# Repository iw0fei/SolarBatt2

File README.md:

# SolarBatt2
Battery Monitor with ESP32 for photovoltaic system

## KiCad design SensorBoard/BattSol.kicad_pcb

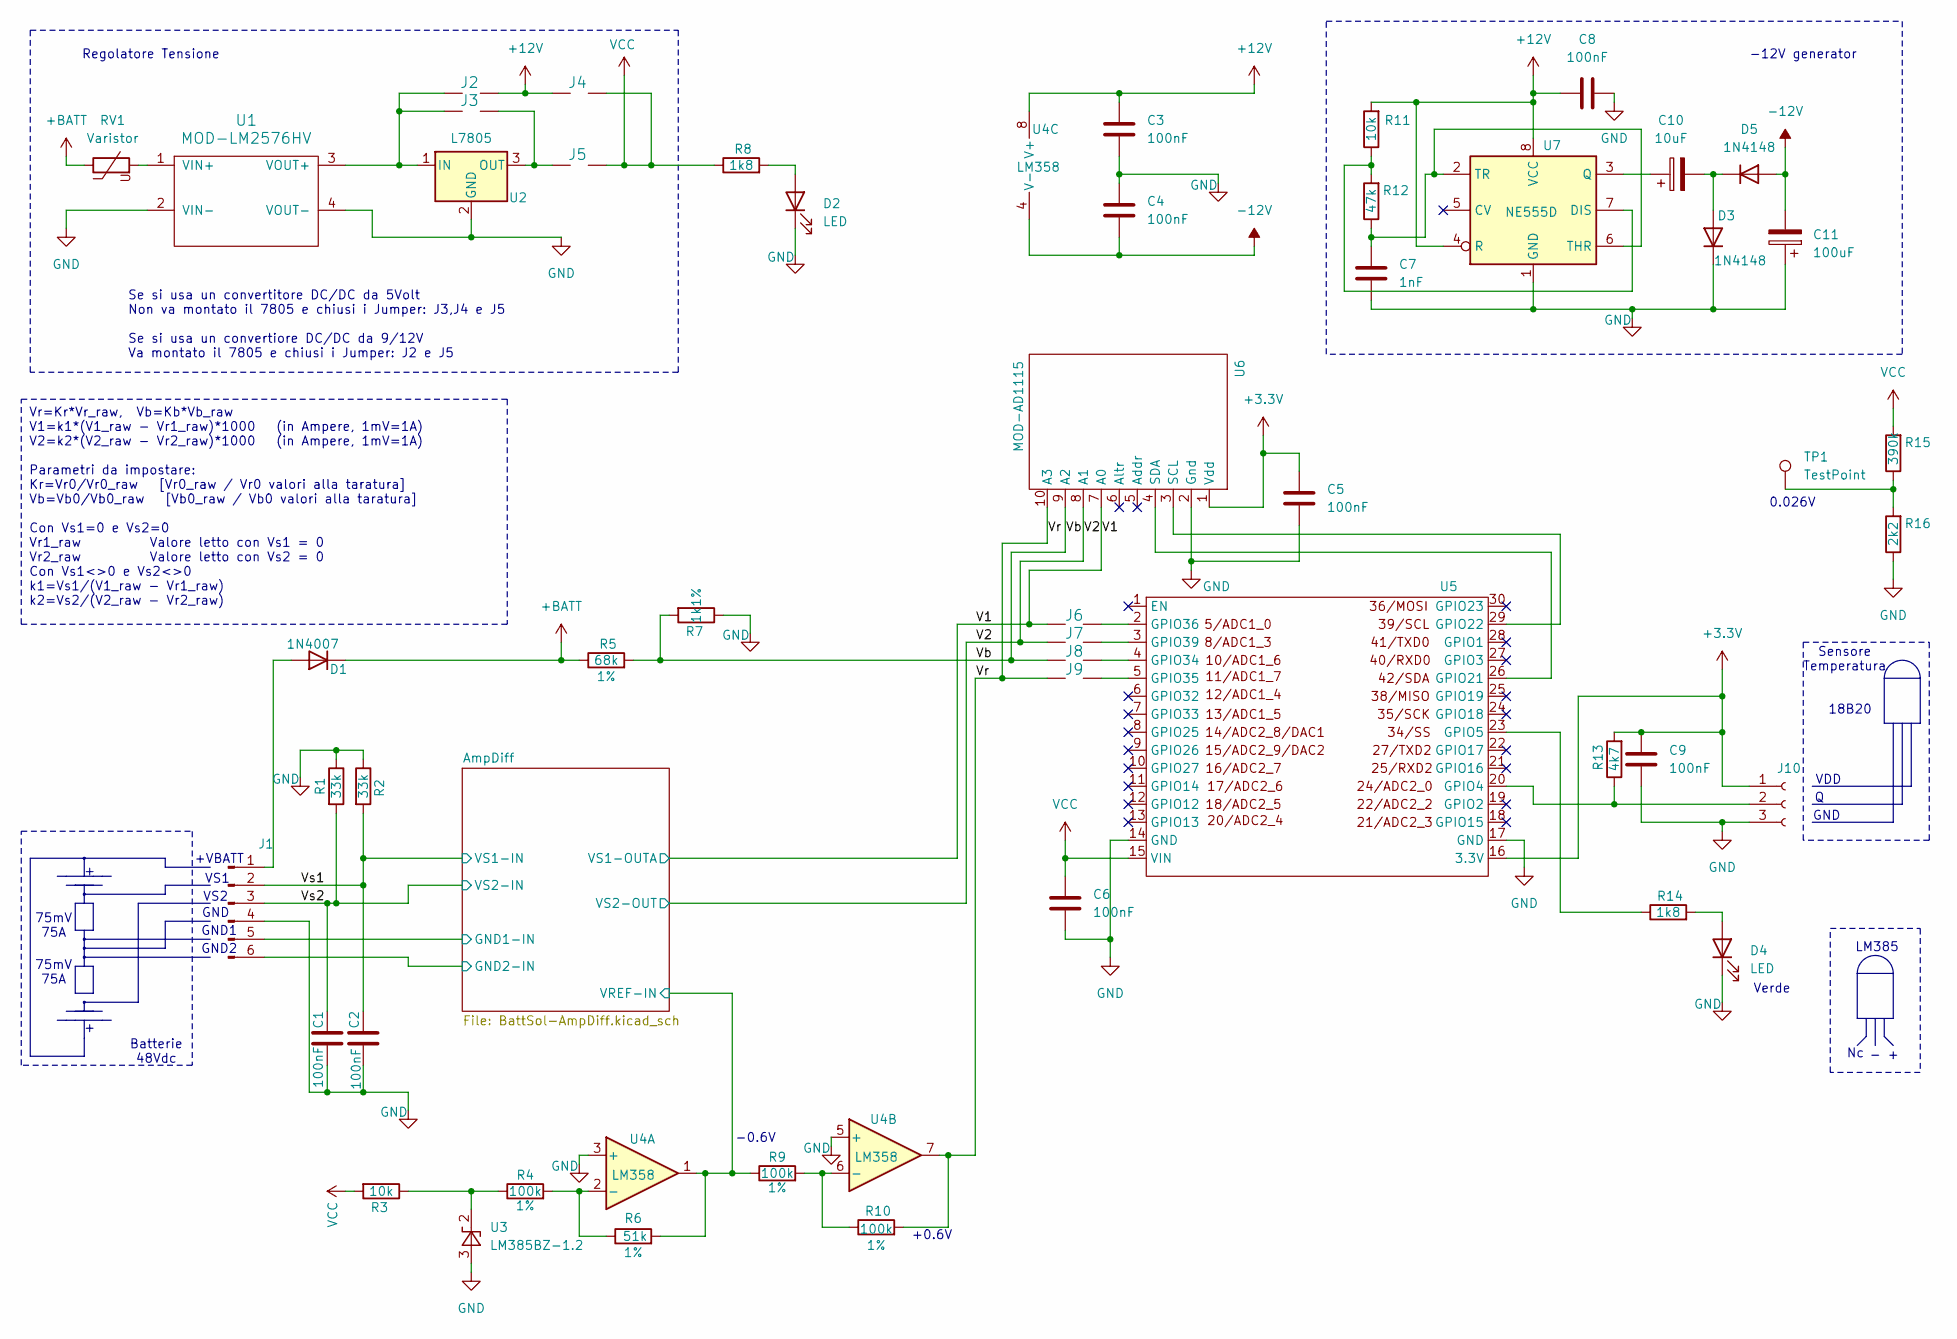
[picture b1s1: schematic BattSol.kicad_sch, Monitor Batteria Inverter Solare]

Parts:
C1, C2, C3, C4, C5, C6, C8, C9: 100nF; C_Rect_L4.6mm_W2.0mm_P2.50mm_MKS02_FKP02
C7: 1nF; C_Rect_L4.6mm_W2.0mm_P2.50mm_MKS02_FKP02
C10: 10uF; CP_Radial_D8.0mm_P5.00mm
C11: 100uF; CP_Radial_D8.0mm_P5.00mm
D1: 1N4007; D_DO-34_SOD68_P5.08mm_Vertical_AnodeUp
D2, D4: LED; LED_D4.0mm
D3, D5: 1N4148; D_DO-34_SOD68_P5.08mm_Vertical_AnodeUp
J1: Conn_01x06_Pin; XCONN_6
J2, J3, J4, J5, J6, J7, J8, J9: JUMPER; XCONN_2
J10: Conn_01x03_Socket; XCONN_3
R1, R2: 33k; R_Axial_DIN0207_L6.3mm_D2.5mm_P7.62mm_Horizontal
R3, R11: 10k; R_Axial_DIN0207_L6.3mm_D2.5mm_P7.62mm_Horizontal
R4, R9, R10: 100k; R_Axial_DIN0207_L6.3mm_D2.5mm_P7.62mm_Horizontal
R5: 68k; R_Axial_DIN0207_L6.3mm_D2.5mm_P7.62mm_Horizontal
R6: 51k; R_Axial_DIN0207_L6.3mm_D2.5mm_P7.62mm_Horizontal
R7: 1k; R_Axial_DIN0207_L6.3mm_D2.5mm_P7.62mm_Horizontal
R8, R14: 1k8; R_Axial_DIN0207_L6.3mm_D2.5mm_P7.62mm_Horizontal
R12: 47k; R_Axial_DIN0207_L6.3mm_D2.5mm_P7.62mm_Horizontal
R13: 4k7; R_Axial_DIN0207_L6.3mm_D2.5mm_P7.62mm_Horizontal
R15: 390k; R_Axial_DIN0207_L6.3mm_D2.5mm_P7.62mm_Horizontal
R16: 2k2; R_Axial_DIN0207_L6.3mm_D2.5mm_P7.62mm_Horizontal
RV1: Varistor; RV_Disc_D7mm_W3.4mm_P5mm
TP1: TestPoint; XCONN_1
U1: MOD-LM2576HV
U2: L7805; TO-3PB-3_Vertical
U3: LM385BZ-1.2; TO-92_Inline
U4: LM358; XDIL_8
U5: ESP32-DEVKIT-V1
U6: MOD-AD1115; MOD-ADS1115
U7: NE555D; CERDIP-8_W7.62mm_SideBrazed_LongPads

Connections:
+3.3V: C5.1, C9.1, J10.1, R13.2, U5.16 (3.3V), U6.1 (Vdd)
+12V: C3.1, C8.1, J2.2, J4.1, R11.2, U4.8 (V+), U7.4 (R), U7.8 (VCC); also elsewhere on the board
+BATT: D1.1 (K), R5.1, RV1.1
-12V: C4.2, C11.2, D5.2 (A), U4.4 (V-); also elsewhere on the board
/AmpDiff/GND1-IN: J1.5; also elsewhere on the board
/AmpDiff/GND2-IN: J1.6; also elsewhere on the board
/AmpDiff/VREF-IN: R6.2, R9.1, U4.1; also elsewhere on the board
/V1: J6.1, U6.7 (A0); also elsewhere on the board
/V2: J7.1, U6.8 (A1); also elsewhere on the board
/Vb: J8.1, R5.2, R7.2, U6.9 (A2)
/Vr: J9.1, R10.2, U4.7, U6.10 (A3)
/Vs1: C2.1, J1.2, R2.2; also elsewhere on the board
/Vs2: C1.1, J1.3, R1.2; also elsewhere on the board
GND: C1.2, C2.2, C3.2, C4.1, C5.2, C6.2, C7.2, C8.2, C9.2, C11.1, D2.1 (K), D3.1 (K), D4.1 (K), J1.4, J10.3, R1.1, R2.1, R7.1, R16.1, U1.2 (VIN-), U1.4 (VOUT-), U2.2 (GND), U3.3 (A), U4.3 (+), U4.5 (+), U5.14 (GND), U5.17 (GND), U6.2 (Gnd), U7.1 (GND); also elsewhere on the board
unnamed: D1.2 (A), J1.1
unnamed: D2.2 (A), R8.2
unnamed: C10.2, D3.2 (A), D5.1 (K)
unnamed: D4.2 (A), R14.2
unnamed: J10.2, R13.1, U5.20 (GPIO4)
unnamed: R15.1, R16.2, TP1.1
unnamed: RV1.2, U1.1 (VIN+)
unnamed: J2.1, J3.1, U1.3 (VOUT+), U2.1 (IN)
unnamed: J3.2, J5.1, U2.3 (OUT)
unnamed: R3.1, R4.1, U3.2 (K)
unnamed: R4.2, R6.1, U4.2 (-)
unnamed: R9.2, R10.1, U4.6 (-)
unnamed: R14.1, U5.23 (GPIO5)
unnamed: U5.26 (GPIO21), U6.4 (SDA)
unnamed: U5.29 (GPIO22), U6.3 (SCL)
unnamed: J8.2, U5.4 (GPIO34)
unnamed: J9.2, U5.5 (GPIO35)
unnamed: J6.2, U5.2 (GPIO36)
unnamed: J7.2, U5.3 (GPIO39)
unnamed: R11.1, R12.2, U7.7 (DIS)
unnamed: C10.1, U7.3 (Q)
unnamed: C7.1, R12.1, U7.2 (TR), U7.6 (THR)
VCC: C6.1, J4.2, J5.2, R3.2, R8.1, R15.2, U5.15 (VIN)

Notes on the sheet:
Vr=Kr*Vr_raw, Vb=Kb*Vb_raw V1=k1*(V1_raw - Vr1_raw)*1000 (in Ampere, 1mV=1A) V2=k2*(V2_raw - Vr2_raw)*1000 (in Ampere, 1mV=1A) Parametri da impostare: Kr=Vr0/Vr0_raw [Vr0_raw / Vr0 valori alla taratura] Vb=Vb0/Vb0_raw [Vb0_raw / Vb0 valori alla taratura] Con Vs1=0 e Vs2=0 Vr1_raw Valore letto con V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
VS2
0.026V
Verde
-12V generator
+0.6V
VS1
75mV 75A
Se si usa un convertitore DC/DC da 5Volt Non va montato il 7805 e chiusi i Jumper: J3,J4 e J5 Se si usa un convertiore DC/DC da 9/12V Va montato il 7805 e chiusi i Jumper: J2 e J5
GND1
Regolatore Tensione
18B20
+VBATT
VDD
Sensore Temperatura
GND
LM385
Batterie 48Vdc
GND2
-0.6V

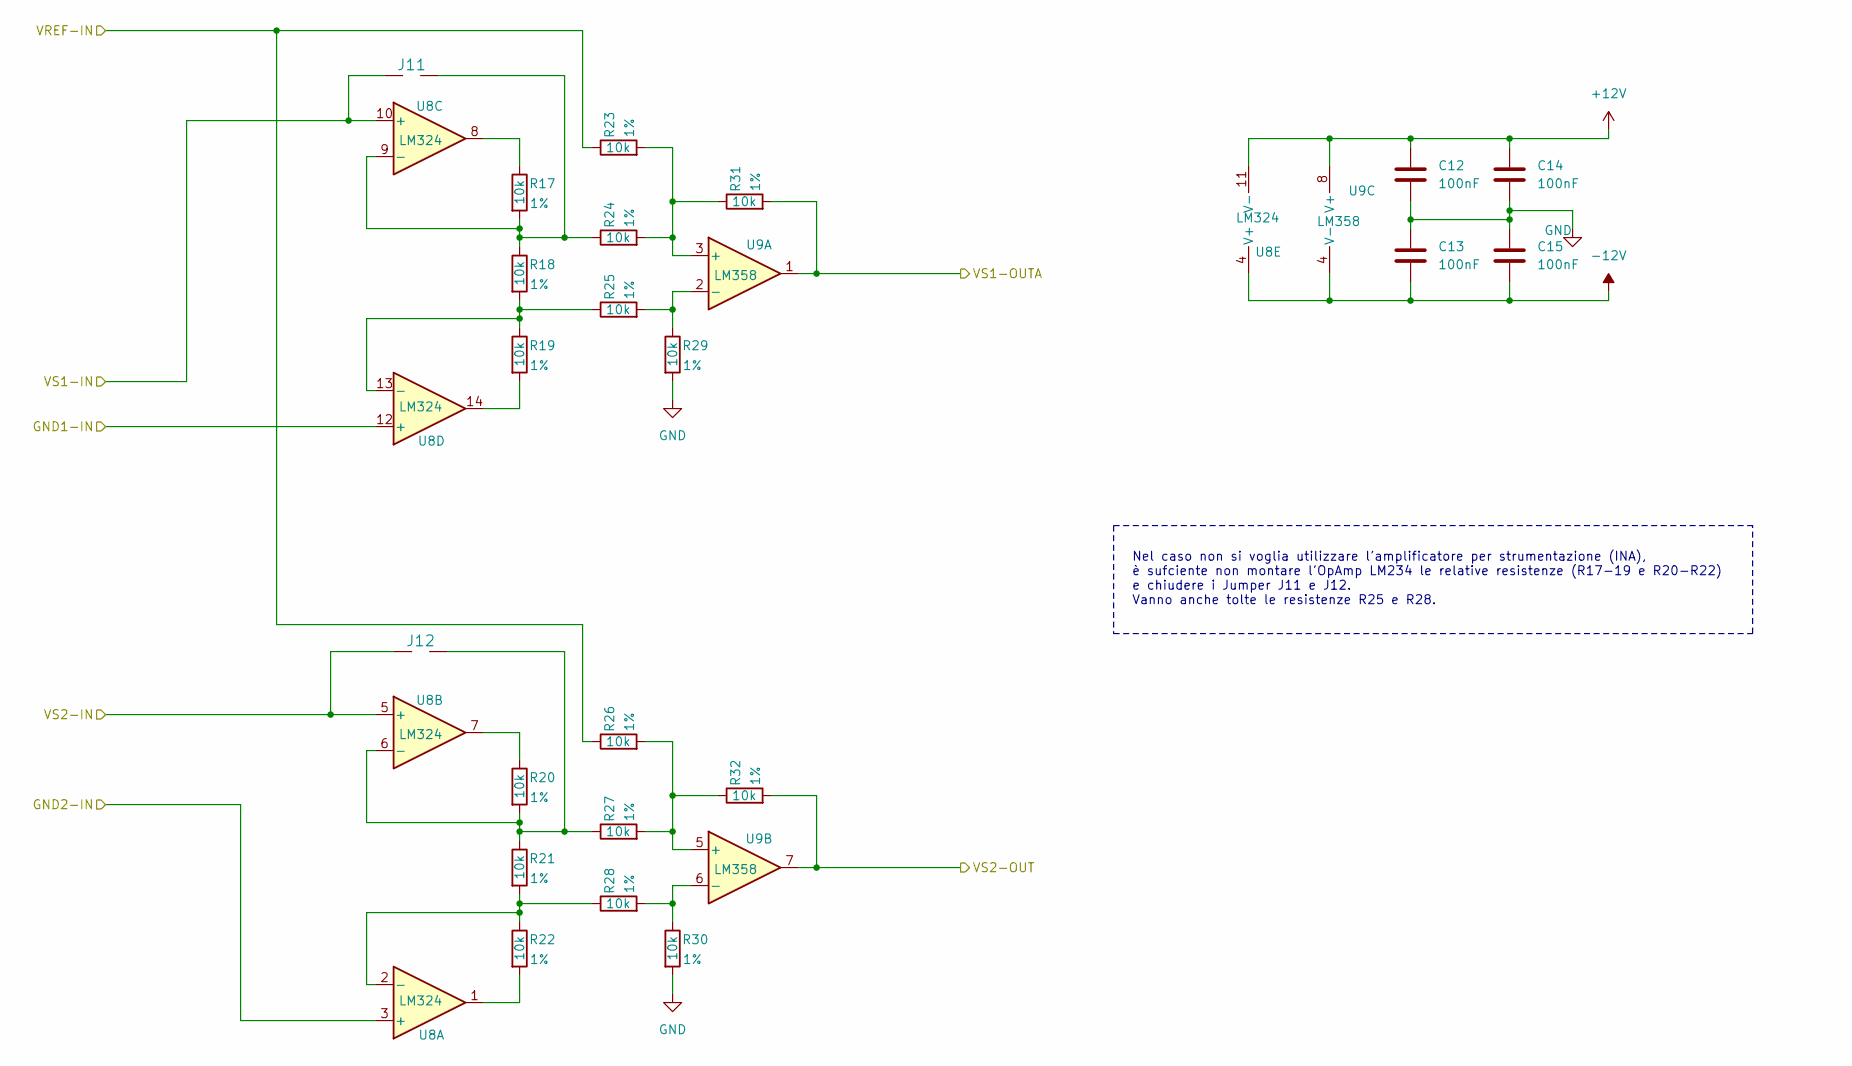
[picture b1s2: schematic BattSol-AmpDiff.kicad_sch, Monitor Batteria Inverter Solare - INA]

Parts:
C12, C13, C14, C15: 100nF; C_Rect_L4.6mm_W2.0mm_P2.50mm_MKS02_FKP02
J11, J12: JUMPER; XCONN_2
R17, R18, R19, R20, R21, R22, R23, R24, R25, R26, R27, R28, R29, R30, R31, R32: 10k; R_Axial_DIN0207_L6.3mm_D2.5mm_P7.62mm_Horizontal
U8: LM324; XDIL_14
U9: LM358; XDIL_8

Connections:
+12V: C12.1, C14.1, U8.11 (V-), U9.8 (V+); also elsewhere on the board
-12V: C13.2, C15.2, U8.4 (V+), U9.4 (V-); also elsewhere on the board
/AmpDiff/GND1-IN: U8.12 (+); also elsewhere on the board
/AmpDiff/GND2-IN: U8.3 (+); also elsewhere on the board
/AmpDiff/VREF-IN: R23.1, R26.1; also elsewhere on the board
/V1: R31.2, U9.1; also elsewhere on the board
/V2: R32.2, U9.7; also elsewhere on the board
/Vs1: J11.1, U8.10 (+); also elsewhere on the board
/Vs2: J12.1, U8.5 (+); also elsewhere on the board
GND: C12.2, C13.1, C14.2, C15.1, R29.2, R30.2; also elsewhere on the board
unnamed: R17.1, U8.8
unnamed: R19.2, U8.14
unnamed: R20.1, U8.7
unnamed: R22.2, U8.1
unnamed: R21.2, R22.1, R28.1, U8.2 (-)
unnamed: J12.2, R20.2, R21.1, R27.1, U8.6 (-)
unnamed: J11.2, R17.2, R18.1, R24.1, U8.9 (-)
unnamed: R18.2, R19.1, R25.1, U8.13 (-)
unnamed: R23.2, R24.2, R31.1, U9.3 (+)
unnamed: R25.2, R29.1, U9.2 (-)
unnamed: R26.2, R27.2, R32.1, U9.5 (+)
unnamed: R28.2, R30.1, U9.6 (-)

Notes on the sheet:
Nel caso non si voglia utilizzare l'amplificatore per strumentazione (INA), è sufciente non montare l'OpAmp LM234 le relative resistenze (R17-19 e R20-R22) e chiudere i Jumper J11 e J12. Vanno anche tolte le resistenze R25 e R28.

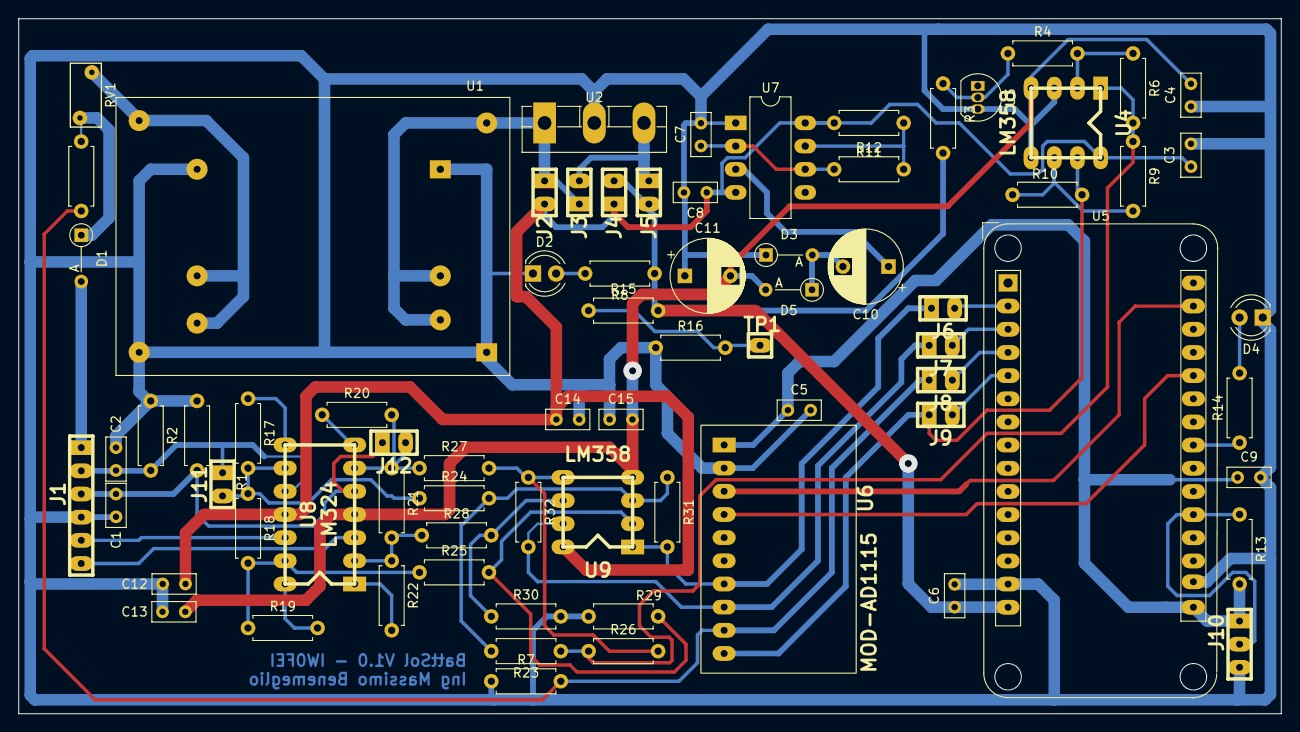
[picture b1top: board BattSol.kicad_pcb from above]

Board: 2 copper layers, 138.4 x 76.2 mm, 75 parts (0 on the bottom side), 49 nets.
